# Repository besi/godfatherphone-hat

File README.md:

# godfatherphone-hat
Raspberry Pi Zero HAT for the Godfatherphone

### Links

[besi/godfatherphone-box](https://github.com/besi/godfatherphone-box)

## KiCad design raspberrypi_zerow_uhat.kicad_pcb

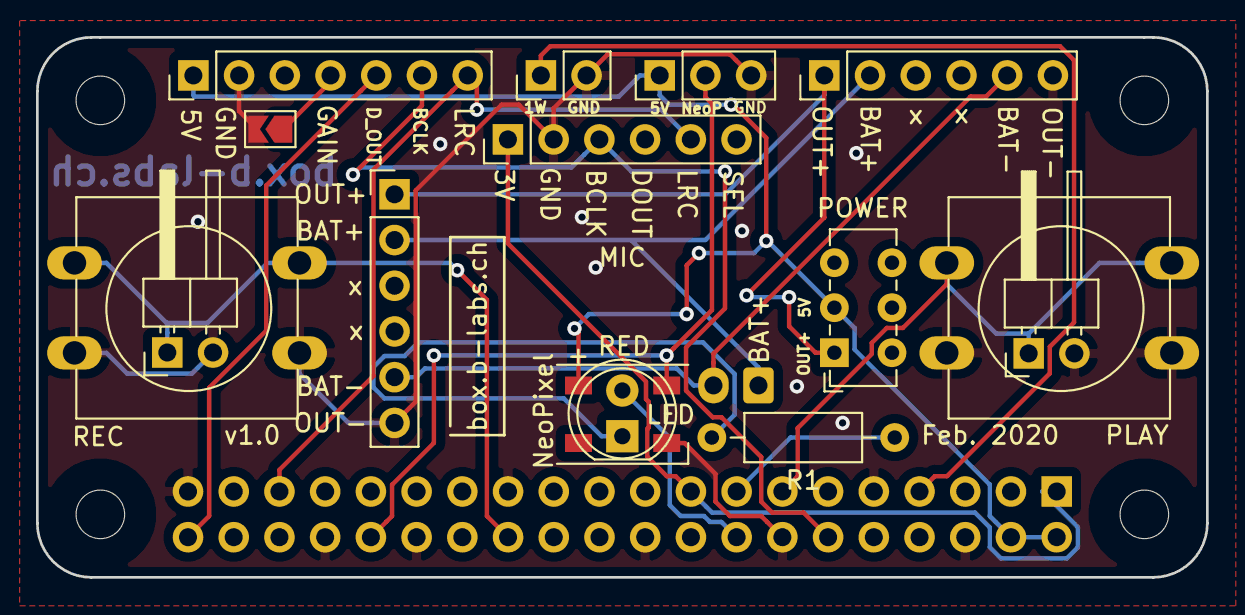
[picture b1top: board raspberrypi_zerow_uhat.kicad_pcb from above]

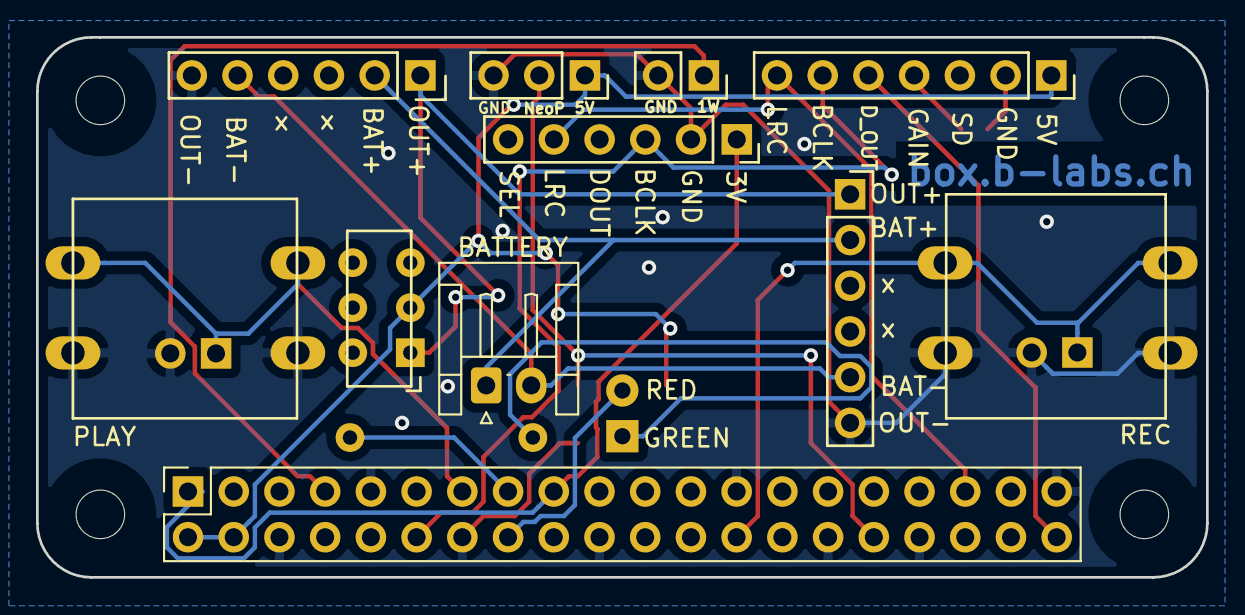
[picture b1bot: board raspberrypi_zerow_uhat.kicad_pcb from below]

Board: 2 copper layers, 65.0 x 30.0 mm, 21 parts (2 on the bottom side), 17 nets.

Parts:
GREEN1: Green; SW_PUSH-12mm
H1, H2, H3, H4: MountingHole; MountingHole_2.7mm_M2.5_uHAT_RPi
J1: GPIO_CONNECTOR; PinSocket_2x20_P2.54mm_Vertical_Centered_Anchor
J2: Amp connector; PinHeader_1x07_P2.54mm_Vertical
J3: Mic connector; PinHeader_1x06_P2.54mm_Vertical
J4: OneWire; PinHeader_1x02_P2.54mm_Vertical
J5: Neopixel connector; PinHeader_1x03_P2.54mm_Vertical
J6: Battery; JST_EH_S2B-EH_1x02_P2.50mm_Horizontal
J7: Voltage Regulator Option A; PinHeader_1x06_P2.54mm_Vertical
J8: Voltage Regulator Option B; PinHeader_1x06_P2.54mm_Vertical
JP1: GainGND; SolderJumper-2_P1.3mm_Open_TrianglePad1.0x1.5mm
J_GREEN1: GREEN; PinHeader_1x02_P2.54mm_Horizontal
J_RED1: RED; PinHeader_1x02_P2.54mm_Horizontal
LED1: LED_Dual_2pin; LED_D5.0mm
Neopixel1: WS2812B; LED_WS2812B_PLCC4_5.0x5.0mm_P3.2mm
R1: 220; R_Axial_DIN0207_L6.3mm_D2.5mm_P10.16mm_Horizontal
RED1: Red; SW_PUSH-12mm
SW1: POWER; SW_E-Switch_EG1271_DPDT

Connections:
+3V3: J1.1, J1.17, J3.1
+5V: J1.2, J1.4, J2.1, J5.1, Neopixel1.1, SW1.2
BAT+: J6.1, J7.2, J8.2
BAT-: J6.2, J7.5, J8.5
BCLK: J1.12, J2.6, J3.3
DATA_AUDIO_OUT: J1.40, J2.5
GAIN: J2.4, JP1.1
GND: GREEN1.2, J1.6, J1.9, J1.14, J1.20, J1.25, J1.30, J1.34, J1.39, J2.2, J3.2, J4.2, J5.3, J7.6, J8.6, JP1.2, J_GREEN1.2, J_RED1.2, Neopixel1.3, RED1.2
GREEN_LED: J1.15, R1.1
GREEN_SWITCH: GREEN1.1, J1.13, J_GREEN1.1
LRC: J1.35, J2.7, J3.5
NEOPIXEL_DATA: J1.32, J5.2, Neopixel1.4
unnamed: LED1.1, R1.2
ONE_WIRE: J1.7, J4.1
OUT+: J7.1, J8.1, SW1.1
RED_LED: J1.16, LED1.2
RED_SWITCH: J1.26, J_RED1.1, RED1.1

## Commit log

2020-02-18 Added central elements
2020-02-24 v1.0
2020-03-12 Added a readme
2021-05-27 Added board.svg

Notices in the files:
raspberrypi_zerow_uhat.kicad_pcb:
This PCB design is licensed under MIT Open Source License.
